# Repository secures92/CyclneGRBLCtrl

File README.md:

CyclneGRBLCtrl
==============

From design to manufactured pcb

FAQ
---

Will your board be machinable on the cyclone ?
- Hopefully yes.. smallest trace is 12mil. maybe double sided will be a bit tricky..

What processor is used ? 
- the same as the arduino uno - Atmega 328 - the board will be fully compatible to the arduino uno r3 and grbl.. all the pins are useable.. except the bootloader.. (Im using the FT230X so the arduino bootloader wont work- maybe the serial converter will be changed .. I have to think about it)..

Will you use the stepstick drivers for the steppers ? 
- of course i´ll use the stepstickdrivers.. (x,y,z), there is also a mosfet for the spindle.. and three endstops .. everything can also be connected over the pins (ability to use external components e.g. spindle driver, motor driver, lcd, even the serial converter to use a bluetooth module..)

Is Z-Probing supported?
- the z probing wont have a seperate connector.. (GRBL dont support it atm) but it can be added through a unused pin..

How to get a PCB?
- http://oshpark.com/shared_projects/NCN02WgN

Licence
---
CC-BY-SA 4.0

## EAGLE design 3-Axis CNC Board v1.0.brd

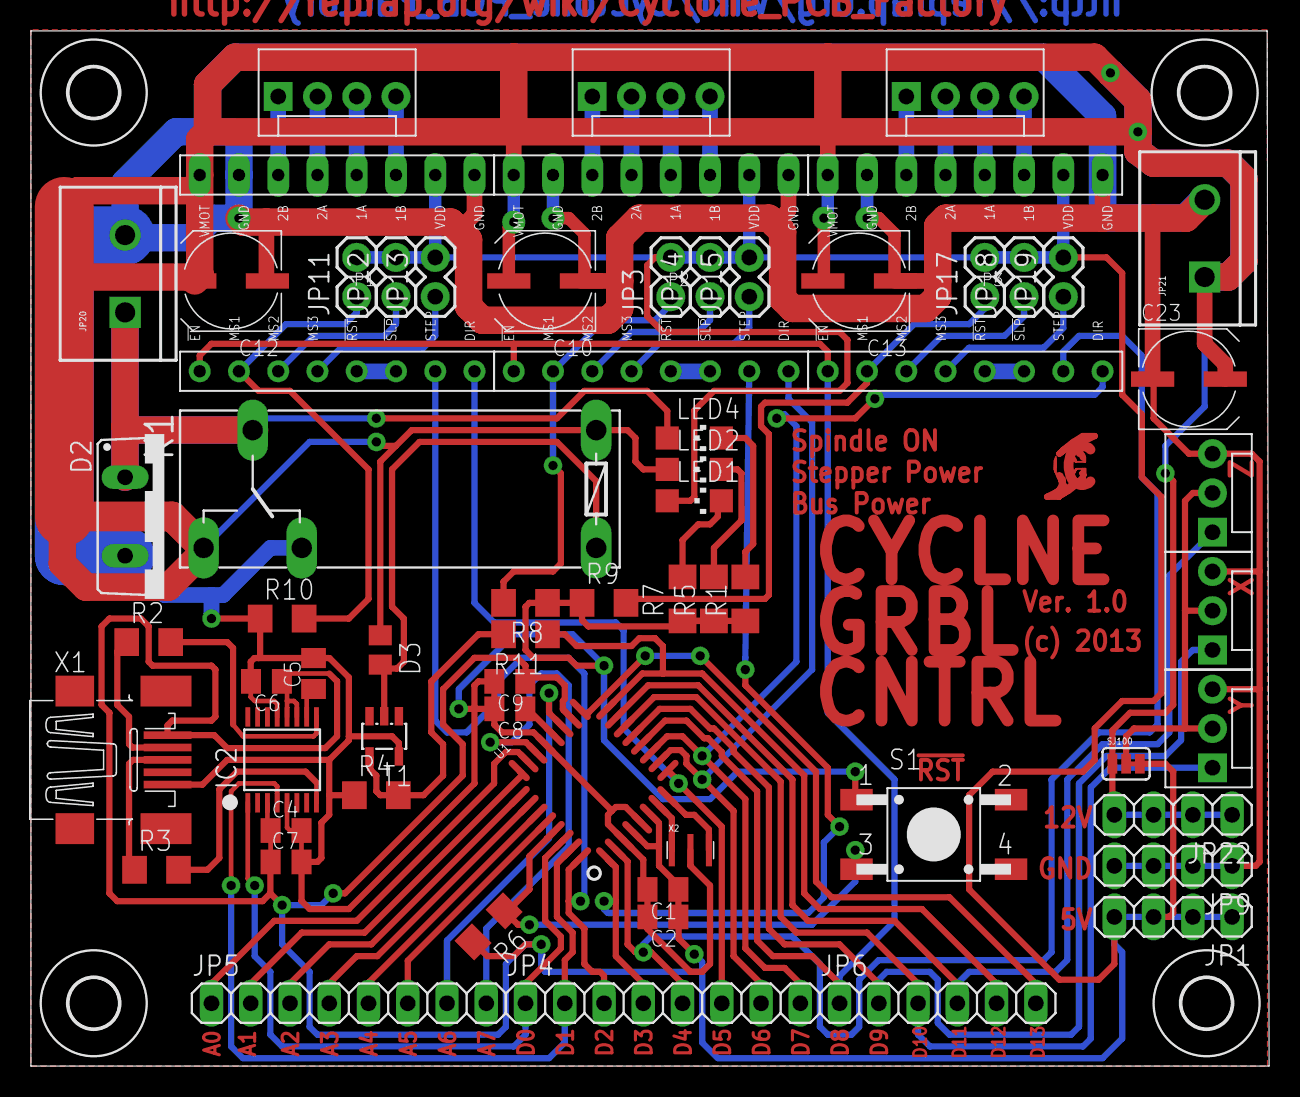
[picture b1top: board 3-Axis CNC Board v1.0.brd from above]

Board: 2 copper layers, 80.1 x 67.0 mm, 66 parts (0 on the bottom side), 65 nets.

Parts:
C1, C2, C5, C6, C8, C9: 100n; C0805K
C4: 10n; C0805K
C7: 4u7; C0805K
C10, C12, C13, C23: 100u; UD-6,3X7,7_NICHICON
D2: MBR1645; TO220ACS
D3: 1N4148; R0805
H1, H2, H3, H4: MOUNT-HOLE3.2; 3,2
IC2: IC_FT230X; SSOP-16-FTDI
JP1, JP9, JP22: 1X04
JP2, JP10, JP16: MOT-X; MOLEX-1X4
JP3: Y-MS1; 1X02
JP4, JP5: 1X08
JP6: 1X06
JP11: X-MS1; 1X02
JP12: X-MS2; 1X02
JP13: X-MS3; 1X02
JP14: Y-MS2; 1X02
JP15: Y-MS3; 1X02
JP17: Z-MS1; 1X02
JP18: Z-MS2; 1X02
JP19: Z-MS3; 1X02
JP20: Spindle; SCREWTERMINAL-5MM-2
JP21: Power; SCREWTERMINAL-5MM-2
JP27: X-STOP; MOLEX-1X3
JP28: Y-STOP; MOLEX-1X3
JP29: Z-STOP; MOLEX-1X3
K1: G6RW
LED1, LED2, LED4: CHIPLED_1206
P1, P2, P3: POLOLU-X; POLOLU-ALLEGRO-PTH
R1, R5: 2k2; R1206
R2, R3: 27; R1206
R4: 100k; R1206
R6, R8, R9, R10: 10k; R1206
R7: 1k; R1206
R11: 22R; R1206
S1: TASTER-9314_SMD
SJ100: 5v/12v; SJ_3
T1: BSS138; SOT23-5L
U1: ATMEGA168-20AU; QFP032
X1: MINI-USB; 32005-201_1
X2: 16MHz; CSTCE_

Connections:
+5V: C1.1, C2.1, C4.1, C6.1, C7.1, C9.1, IC2.3, IC2.11, IC2.12, JP1.1, JP1.2, JP1.3, JP1.4, JP3.2, JP11.2, JP12.2, JP13.2, JP14.2, JP15.2, JP17.2, JP18.2, JP19.2, LED1.A, P1.VDD, P2.VDD, P3.VDD, R6.2, SJ100.3, U1.4, U1.6, U1.18, X1.1
A0: JP5.1, U1.23
A1: JP5.2, U1.24
A2: JP5.3, U1.25
A3: JP5.4, U1.26
A4: JP5.5, U1.27
A5: JP5.6, U1.28
A6: JP5.7, U1.19
A7: JP5.8, U1.22
AREF: C8.1, U1.20
D0/RX: IC2.1, JP4.1, U1.30
D1/TX: IC2.4, JP4.2, U1.31
D2/STEPX: JP4.3, P1.STEP, U1.32
D3/STEPY: JP4.4, P2.STEP, U1.1
D4/STEPZ: JP4.5, P3.STEP, U1.2
D5/DIRX: JP4.6, P1.DIR, U1.9
D6/DIRY: JP4.7, P2.DIR, U1.10
D7/DIRZ: JP4.8, P3.DIR, U1.11
D8/ENA: JP6.1, P1.!EN, P2.!EN, P3.!EN, U1.12
D9/LIMITX: JP6.2, JP27.1, U1.13
D10/LIMITY: JP6.3, JP28.1, U1.14
D11/MOSI: JP6.4, JP29.1, U1.15
D12/MISO: JP6.5, R11.1, U1.16
D13/SCK: JP6.6, U1.17
D+: IC2.8, R3.2
D-: IC2.9, R2.2
ENDSTOP+V: JP27.2, JP28.2, JP29.2, SJ100.2
GND: C1.2, C2.2, C4.2, C5.2, C6.2, C7.2, C8.2, C9.2, C10.-, C12.-, C13.-, C23.-, D2.A, IC2.5, IC2.13, JP9.1, JP9.2, JP9.3, JP9.4, JP20.2, JP21.2, JP27.3, JP28.3, JP29.3, K1.O, P1.GNDMOT, P1.GNDVDD, P2.GNDMOT, P2.GNDVDD, P3.GNDMOT, P3.GNDVDD, R1.1, R4.1, R5.1, R7.1, R8.1, R9.1, R10.1, S1.1, T1.5, U1.3, U1.5, U1.21, X1.5, X2.2
unnamed: U1.8, X2.3
unnamed: U1.7, X2.1
unnamed: R3.1, X1.3
unnamed: D3.A, K1.2, T1.2
unnamed: D2.C, JP20.1, K1.P, LED4.A
unnamed: LED1.C, R7.2
unnamed: C5.1, IC2.10
unnamed: R2.1, X1.2
unnamed: LED4.C, R1.2
unnamed: R4.2, R11.2, T1.4
unnamed: LED2.C, R5.2
RESET: R6.1, S1.3, U1.29
V+: C10.+, C12.+, C13.+, C23.+, D3.K, JP21.1, JP22.1, JP22.2, JP22.3, JP22.4, K1.1, K1.S, LED2.A, P1.VMOT, P2.VMOT, P3.VMOT, SJ100.1
X-MOT-1A: JP10.3, P1.1A
X-MOT-1A1: JP2.3, P2.1A
X-MOT-1A2: JP16.3, P3.1A
X-MOT-1B: JP10.4, P1.1B
X-MOT-1B1: JP2.4, P2.1B
X-MOT-1B2: JP16.4, P3.1B
X-MOT-2A: JP10.2, P1.2A
X-MOT-2A1: JP2.2, P2.2A
X-MOT-2A2: JP16.2, P3.2A
X-MOT-2B: JP10.1, P1.2B
X-MOT-2B1: JP2.1, P2.2B
X-MOT-2B2: JP16.1, P3.2B
X-MS1: JP11.1, P1.MS1, R10.2
X-MS2: JP12.1, P1.MS2
X-MS3: JP13.1, P1.MS3
X-MS4: JP14.1, P2.MS2
X-MS5: JP15.1, P2.MS3
X-MS6: JP3.1, P2.MS1, R8.2
X-MS7: JP18.1, P3.MS2
X-MS8: JP19.1, P3.MS3
X-MS9: JP17.1, P3.MS1, R9.2
X-RESETSLEEP: P1.!RST, P1.!SLP
X-RESETSLEEP1: P2.!RST, P2.!SLP
X-RESETSLEEP2: P3.!RST, P3.!SLP

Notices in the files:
3-Axis CNC Board v1.0.brd:
(c) 2013
parts and their libraries:
SparkFun-Connectors: Licensing: CC v3.0 Share-Alike You are welcome to use this library for commercial purposes.
